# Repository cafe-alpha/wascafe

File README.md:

# wascafe

Wascafe ?
cafe-alpha's sandbox for wasca project, where I put sources for each PCB revision in a separate folder, and also where I learn how to use github related things.

Wasca ?
Sega Saturn multipurpose cartridge, still in development phase.
It will mimic Power Memory / Backup RAM, 1MB ROMs from KoF and Ultraman, and 1M/4M RAM expansion.
More than that, it should emulate Sega Saturn modems, and launch any 3rd party code, for example PseudoSaturn Kai.
Cart is based on Altera MAX 10 FPGA with external SDRAM and internal Nios II soft CPU. 

Wasca main repository can be found here : https://github.com/hitomi2500/wasca/

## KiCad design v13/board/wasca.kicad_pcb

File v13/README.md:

# Wasca version 1.3, by cafe-alpha, Autumn 2018

## Differences with v1.2
 - Communication with PC via FTDI
 - Expansion RAM emulation ... not working well
 - Stub of SPI communication with STM32 ... chip not available in this board

## About each directories
 - board : PCB sources
 - wasca_10m08scv4k_no_spi_20190420 : "stable" version of the firmware with only a minimal set of functions working.
 - wasca_10m08sc_20191205_abus_divide : attempt to make expansion RAM working ... which breaks several things.
 - WascaLoader : test bench for use on Saturn side, which contains several functionalities to test expansion RAM.

## How to compile firmware
 1. Quartus version used : 15.1.2 Lite
 2. Rebuild Qsys sources
 3. Compile the project
 4. In software -> wasca_test9 folder, load mk.bat
 5. Type "rb" and enter to rebuild NIOS part of the firmware

## Pictures :

More pictures and informations available on [my Saturn cartridges gallery](https://ppcenter.webou.net/satcart/gallery/#revw13).

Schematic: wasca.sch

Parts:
C1, C4: 4.7uF; C_0603_HandSoldering
C2, C3, C5, C6, C7, C8, C12, C13, C15, C40, C43, C45, C48, C49, C50, C51, C151, C152, C154: 0.1uF; SM0603
C16: 10uF; C_1206_HandSoldering
C29, C30, C31, C32, C33, C34, C35, C36, C37, C38, C39, C41, C42, C44, C46, C47: 0.1uF; C_0603_HandSoldering
C91, C153: 4.7uF; SM0603
CN1: CARTRIDGE_EDGE_CONNECTOR; CARTRIDGE_EDGE_CONNECTOR2
JTAG1: AVR-JTAG-10; JTAG_Header
LEDG1: LED; LED-3MM
LEDO1: LED; LED_0805
LEDR1: LED; LED-3MM
R12, R13, R14: 10K; R_0603_HandSoldering
R15: 1K; SM0603
R16, R17, R61, R62, R153: 10K; SM0603
R91, R92: 51K; SM0603
R152: 4K7; SM0603
R155, R156: 470; SM0603
R421, R422, R423: 470; R_0603_HandSoldering
RX_LED1: LED; LED_0805
SD1: SD_CARD; sd_socket
SW1: SWITCH_INV; NINJA_SW
TX_LED1: LED; LED_0805
U1, U2, U3, U4, U11: 74ALVC164245; TSSOP-48_6.1x12.5mm_Pitch0.5mm
U5: LD1117S33CTR; SOT-223
U8: 10M08SCE144I7G; TQFP144_ALTERA_HANDSOLDERING
U9: SDRAM_MT48_x16; TSOPII54_SDRAM_MT48
U151: FT232RL; SSOP28
X1, X61: CONN_02X02; Pin_Header_Straight_2x02
X2: CONN_01X02; Pin_Header_Straight_1x02_Pitch2.54mm
X4: CONN_01X04; Pin_Header_Straight_1x04
X151: USB-MB-S; con-usb-USB-MB-S

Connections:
/+3_3V: C5.1, C6.1, C12.1, C13.1, C16.1, C29.1, C30.1, C31.1, C32.1, C33.1, C34.1, C35.1, C36.1, C37.1, C38.1, C39.1, C40.1, C41.1, C42.1, C43.1, C44.1, C45.1, C46.1, C47.1, C48.1, C49.1, C51.1, C91.1, JTAG1.4, R12.1, R13.1, R14.1, R16.1, R17.1, R61.1, R62.1, R91.1, R92.1, RX_LED1.2 (A), SD1.4 (VDD), TX_LED1.2 (A), U1.31 (VCCA), U1.42 (VCCA), U2.31 (VCCA), U2.42 (VCCA), U3.24 (2DIR), U3.31 (VCCA), U3.42 (VCCA), U4.31 (VCCA), U4.42 (VCCA), U5.2 (VO), U8.1 (VCC_ONE), U8.2 (VCCA6), U8.5 (VCCA3), U8.9 (VCCO1A), U8.23 (VCCO1B), U8.31 (VCCO2), U8.34 (VCCA2), U8.35 (VCCA1), U8.36 (VCC_ONE), U8.37 (VCC_ONE), U8.40 (VCCO3), U8.49 (VCCO3), U8.51 (VCC_ONE), U8.67 (VCCO4), U8.71 (VCCA5), U8.72 (VCC_ONE), U8.73 (VCC_ONE), U8.82 (VCCO5), U8.94 (VCCO6), U8.103 (VCCO6), U8.107 (VCCA3), U8.108 (VCC_ONE), U8.109 (VCC_ONE), U8.115 (VCC_ONE), U8.117 (VCCO7), U8.128 (VCCO8), U8.139 (VCCO8), U8.143 (VCCA4), U8.144 (VCC_ONE), U9.1 (VDD), U9.3 (VDD), U9.9 (VDD), U9.14 (VDD), U9.27 (VDD), U9.43 (VDD), U9.49 (VDD), U11.1 (1DIR), U11.31 (VCCA), U11.42 (VCCA), U151.4 (VCCIO), X1.2
/+5V: C1.1, C2.1, C3.1, C4.1, C7.1, C8.1, C15.1, C50.1, C151.1, C152.1, C153.1, CN1.A1 (VCC), CN1.A2 (VCC), CN1.A27 (VCC), CN1.A67 (VCC), CN1.B1 (VCC), CN1.B2 (VCC), CN1.B27 (VCC), CN1.B67 (VCC), U1.7 (VCCB), U1.18 (VCCB), U2.7 (VCCB), U2.18 (VCCB), U3.7 (VCCB), U3.18 (VCCB), U4.7 (VCCB), U4.18 (VCCB), U5.3 (VI), U11.7 (VCCB), U11.18 (VCCB), U151.20 (VCC), X1.4
/ABUS_3V_A16: U2.41 (1A4), U8.120 (DIFFIO_RX_T16p)
/ABUS_3V_A17: U2.40 (1A5), U8.119 (DIFFIO_RX_T10n)
/ABUS_3V_A18: U2.43 (1A3), U8.121 (DEV_CLRn/DIFFIO_RX_T16n)
/ABUS_3V_A19: U8.118 (DIFFIO_RX_T10p), U11.29 (2A5)
/ABUS_3V_A20: U2.44 (1A2), U8.122 (DEV_OE)
/ABUS_3V_A21: U8.114 (IO), U11.30 (2A4)
/ABUS_3V_A22: U2.46 (1A1), U8.123 (VREFB8N0)
/ABUS_3V_A23: U8.113 (IO), U11.32 (2A3)
/ABUS_3V_A24: U2.47 (1A0), U8.124 (DIFFIO_RX_T19p)
/ABUS_3V_A25: U8.112 (VREFB7N0), U11.33 (2A2)
/ABUS_3V_CS0: U3.40 (1A5), U8.132 (DIFFIO_RX_T22p)
/ABUS_3V_CS1: U3.46 (1A1), U8.127 (DIFFIO_RX_T19n)
/ABUS_3V_CS2: U3.41 (1A4), U8.131 (DIFFIO_RX_T20n)
/ABUS_3V_IRQ: U3.35 (2A1), U8.135 (IO)
/ABUS_3V_MUX0: U1.36 (2A0), U1.37 (1A7), U8.141 (DIFFIO_RX_T26n)
/ABUS_3V_MUX1: U1.35 (2A1), U1.38 (1A6), U8.140 (DIFFIO_RX_T26p)
/ABUS_3V_MUX2: R12.2, U1.33 (2A2), U1.40 (1A5), U8.138 (CONF_DONE/DIFFIO_RX_T24n)
/ABUS_3V_MUX3: U1.32 (2A3), U1.41 (1A4), U8.6 (DIFFIO_RX_L1n)
/ABUS_3V_MUX4: U4.32 (2A3), U4.41 (1A4), U8.17 (VREFB1N0)
/ABUS_3V_MUX5: U4.33 (2A2), U4.40 (1A5), U8.15 (JTAGEN)
/ABUS_3V_MUX6: U4.35 (2A1), U4.38 (1A6), U8.14 (DIFFIO_RX_L7p)
/ABUS_3V_MUX7: U4.36 (2A0), U4.37 (1A7), U8.13 (DIFFIO_RX_L7n)
/ABUS_3V_MUX8: U1.30 (2A4), U1.43 (1A3), U8.7 (DIFFIO_RX_L1p)
/ABUS_3V_MUX9: U1.29 (2A5), U1.44 (1A2), U8.8 (DIFFIO_RX_L3n)
/ABUS_3V_MUX10: U1.27 (2A6), U1.46 (1A1), U8.10 (DIFFIO_RX_L3p)
/ABUS_3V_MUX11: U1.26 (2A7), U1.47 (1A0), U8.11 (DIFFIO_RX_L5n)
/ABUS_3V_MUX12: U4.26 (2A7), U4.47 (1A0), U8.26 (CLK0n/DIFFIO_RX_L18n)
/ABUS_3V_MUX13: U4.27 (2A6), U4.46 (1A1), U8.24 (DIFFIO_RX_L16n)
/ABUS_3V_MUX14: U4.29 (2A5), U4.44 (1A2), U8.22 (DIFFIO_RX_L14p)
/ABUS_3V_MUX15: U4.30 (2A4), U4.43 (1A3), U8.21 (DIFFIO_RX_L14n)
/ABUS_3V_MUX_DATA_DIR: U1.1 (1DIR), U4.24 (2DIR), U8.12 (DIFFIO_RX_L5p)
/ABUS_3V_MUX_EN1: U1.25 (2OE), U4.48 (1OE), U8.25 (DIFFIO_RX_L16p)
/ABUS_3V_MUX_EN2: U1.48 (1OE), U4.25 (2OE), U8.27 (CLK0p/DIFFIO_RX_L18p`)
/ABUS_3V_RD: U3.47 (1A0), U8.126 (CONFIG_SEL)
/ABUS_3V_WAIT: U3.36 (2A0), U8.134 (CRC_ERROR/DIFFIO_RX_T22n)
/ABUS_3V_WR0: U3.43 (1A3), U8.130 (DIFFIO_RX_T20p)
/ABUS_3V_WR1: R14.2, U3.44 (1A2), U8.129 (nCONFIG)
/ABUS_A0: CN1.B45 (AA0), U4.12 (1B7)
/ABUS_A1: CN1.A45 (AA1), U1.13 (2B0)
/ABUS_A2: CN1.B44 (AA2), U4.11 (1B6)
/ABUS_A3: CN1.B43 (AA3), U4.9 (1B5)
/ABUS_A4: CN1.B42 (AA4), U4.8 (1B4)
/ABUS_A5: CN1.B40 (AA5), U4.6 (1B3)
/ABUS_A6: CN1.B39 (AA6), U4.5 (1B2)
/ABUS_A7: CN1.B38 (AA7), U4.3 (1B1)
/ABUS_A8: CN1.A40 (AA8), U1.19 (2B4)
/ABUS_A9: CN1.A42 (AA9), U1.17 (2B3)
/ABUS_A10: CN1.A44 (AA10), U1.14 (2B1)
/ABUS_A11: CN1.A43 (AA11), U1.16 (2B2)
/ABUS_A12: CN1.A38 (AA12), U1.22 (2B6)
/ABUS_A13: CN1.A39 (AA13), U1.20 (2B5)
/ABUS_A14: CN1.B37 (AA14), U4.2 (1B0)
/ABUS_A15: CN1.A37 (AA15), U1.23 (2B7)
/ABUS_A16: CN1.B35 (AA16), U2.8 (1B4)
/ABUS_A17: CN1.A35 (AA17), U2.9 (1B5)
/ABUS_A18: CN1.B34 (AA18), U2.6 (1B3)
/ABUS_A19: CN1.A34 (AA19), U11.20 (2B5)
/ABUS_A20: CN1.B33 (AA20), U2.5 (1B2)
/ABUS_A21: CN1.A33 (AA21), U11.19 (2B4)
/ABUS_A22: CN1.B32 (AA22), U2.3 (1B1)
/ABUS_A23: CN1.A32 (AA23), U11.17 (2B3)
/ABUS_A24: CN1.B31 (AA24), U2.2 (1B0)
/ABUS_A25: CN1.A31 (AA25), U11.16 (2B2)
/ABUS_CS0: CN1.A47 (ACS0), U3.9 (1B5)
/ABUS_CS1: CN1.B48 (ACS1), U3.3 (1B1)
/ABUS_CS2: CN1.A48 (ACS2), U3.8 (1B4)
/ABUS_D0: CN1.A55 (AD0), U1.12 (1B7)
/ABUS_D1: CN1.A56 (AD1), U1.11 (1B6)
/ABUS_D2: CN1.A57 (AD2), U1.9 (1B5)
/ABUS_D3: CN1.A58 (AD3), U1.8 (1B4)
/ABUS_D4: CN1.B58 (AD4), U4.17 (2B3)
/ABUS_D5: CN1.B57 (AD5), U4.16 (2B2)
/ABUS_D6: CN1.B56 (AD6), U4.14 (2B1)
/ABUS_D7: CN1.B55 (AD7), U4.13 (2B0)
/ABUS_D8: CN1.A60 (AD8), U1.6 (1B3)
/ABUS_D9: CN1.A61 (AD9), U1.5 (1B2)
/ABUS_D10: CN1.A62 (AD10), U1.3 (1B1)
/ABUS_D11: CN1.A63 (AD11), U1.2 (1B0)
/ABUS_D12: CN1.B63 (AD12), U4.23 (2B7)
/ABUS_D13: CN1.B62 (AD13), U4.22 (2B6)
/ABUS_D14: CN1.B61 (AD14), U4.20 (2B5)
/ABUS_D15: CN1.B60 (AD15), U4.19 (2B4)
/ABUS_IRQ: CN1.B53 (AIRQ), U3.14 (2B1)
/ABUS_RD: CN1.B47 (ARD), U3.2 (1B0)
/ABUS_WAIT: CN1.B52 (AWAIT), U3.13 (2B0)
/ABUS_WR0: CN1.A49 (AWR0), U3.6 (1B3)
/ABUS_WR1: CN1.B49 (AWR1), U3.5 (1B2)
/DDR_SPARE1: LEDO1.2 (A), U8.99 (DIFFIO_RX_R27p)
/DDR_SPARE2: R62.2, U8.100 (DIFFIO_RX_R28p), X61.3
/DDR_SPARE3: R61.2, SW1.2, U8.101 (DIFFIO_RX_R27n), X61.1
/IBCK: CN1.A5 (IBCK), U11.5 (1B2)
/IBCK_3V: U8.106 (DIFFIO_RX_R33n), U11.44 (1A2)
/ILRCK: CN1.A6 (ILRCK), U11.12 (1B7)
/ILRCK_3V: U8.110 (DIFFIO_RX_T1p), U11.37 (1A7)
/ISD: CN1.A4 (ISD), U11.3 (1B1)
/ISD_3V: U8.105 (DIFFIO_RX_R33p), U11.46 (1A1)
/JTAG_TCK: JTAG1.1, R15.1, U8.18 (TCK/DIFFIO_RX_L11p)
/JTAG_TDI: JTAG1.9, R17.2, U8.19 (TDI/DIFFIO_RX_L12n)
/JTAG_TDO: JTAG1.3, U8.20 (TDO/DIFFIO_RX_L12p)
/JTAG_TMS: JTAG1.5, R16.2, U8.16 (TMS/DIFFIO_RX_L11n)
/LEDG1: LEDG1.2 (A), U8.97 (VREFB6N0)
/LEDR1: LEDR1.2 (A), U8.98 (DPCLK2/DIFFIO_RX_R26n)
/M10_SPARE1: U8.29 (CLK1p/DIFFIO_RX_L20p), X2.1
/M10_SPARE2: U8.30 (VREFB2N0), X2.2
/M10_UART_RX: U8.32 (PLL_L_CLKOUTn/DIFFIO_RX_L27n), U151.1 (TXD)
/M10_UART_TX: U8.33 (PLL_L_CLKOUTp/DIFFIO_RX_L27p), U151.5 (RXD)
/RESET: CN1.A3 (SYSRES), U11.13 (2B0)
/RESET_3V: U8.111 (DIFFIO_RX_T1n), U11.36 (2A0)
/SCSPCLK: CN1.A7 (SCSPCLK), U2.23 (2B7)
/SCSPCLK_3V: U2.26 (2A7), U8.28 (CLK1n/DIFFIO_RX_L20n)
/SDR_A0: U8.65 (DIFFIO_TX_RX_B23p), U9.23 (A0)
/SDR_A1: U8.66 (IO), U9.24 (A1)
/SDR_A2: U8.69 (DIFFIO_TX_RX_B27n), U9.25 (A2)
/SDR_A3: U8.70 (DIFFIO_TX_RX_B27p), U9.26 (A3)
/SDR_A4: U8.96 (DPCLK3/DIFFIO_RX_R26p), U9.29 (A4)
/SDR_A5: U8.93 (DIFFIO_RX_R18n), U9.30 (A5)
/SDR_A6: U8.92 (DIFFIO_RX_R18p), U9.31 (A6)
/SDR_A7: U8.91 (CLK3n/DIFFIO_RX_R16n), U9.32 (A7)
/SDR_A8: U8.90 (CLK3p/DIFFIO_RX_R16p), U9.33 (A8)
/SDR_A9: U8.89 (CLK2n/DIFFIO_RX_R14n), U9.34 (A9)
/SDR_A10: U8.64 (DIFFIO_TX_RX_B23n), U9.22 (A10)
/SDR_A11: U8.88 (CLK2p/DIFFIO_RX_R14p), U9.35 (A11)
/SDR_A12: U8.87 (DIFFIO_RX_R10n), U9.36 (A12)
/SDR_BA0: U8.61 (VREFB4N0), U9.20 (BA0)
/SDR_BA1: U8.62 (IO), U9.21 (BA1)
/SDR_CAS: U8.58 (DIFFIO_TX_RX_B14p), U9.17 (nCAS)
/SDR_CKE: U8.86 (DIFFIO_RX_R11n), U9.37 (CKE)
/SDR_CLK: U8.85 (DIFFIO_RX_R10p), U9.38 (CLK)
/SDR_CS: U8.60 (DIFFIO_TX_RX_B16p), U9.19 (nCS)
/SDR_DQ0: U8.45 (DIFFIO_TX_RX_B5p), U9.2 (DQ0)
/SDR_DQ1: U8.46 (DIFFIO_TX_RX_B7n), U9.4 (DQ1)
/SDR_DQ2: U8.47 (DIFFIO_TX_RX_B7p), U9.5 (DQ2)
/SDR_DQ3: U8.48 (VREFB3N0), U9.7 (DQ3)
/SDR_DQ4: U8.50 (DIFFIO_TX_RX_B9n), U9.8 (DQ4)
/SDR_DQ5: U8.52 (DIFFIO_TX_RX_B9p), U9.10 (DQ5)
/SDR_DQ6: U8.54 (IO), U9.11 (DQ6)
/SDR_DQ7: U8.55 (DIFFIO_TX_RX_B12n), U9.13 (DQ7)
/SDR_DQ8: U8.81 (DIFFIO_RX_R7n), U9.42 (DQ8)
/SDR_DQ9: U8.80 (VREFB5N0), U9.44 (DQ9)
/SDR_DQ10: U8.79 (DIFFIO_RX_R7p), U9.45 (DQ10)
/SDR_DQ11: U8.78 (IO), U9.47 (DQ11)
/SDR_DQ12: U8.77 (DIFFIO_RX_R1n), U9.48 (DQ12)
/SDR_DQ13: U8.76 (DIFFIO_RX_R2n), U9.50 (DQ13)
/SDR_DQ14: U8.75 (DIFFIO_RX_R1p), U9.51 (DQ14)
/SDR_DQ15: U8.74 (DIFFIO_RX_R2p), U9.53 (DQ15)
/SDR_DQMH: U8.84 (DIFFIO_RX_R11p), U9.39 (UDQM-DQMH)
/SDR_DQML: U8.56 (DIFFIO_TX_RX_B12p), U9.15 (LDQM-DQML)
/SDR_RAS: U8.59 (DIFFIO_TX_RX_B16n), U9.18 (nRAS)
/SDR_WE: U8.57 (DIFFIO_TX_RX_B14n), U9.16 (nWE)
/SD_CLK: SD1.5 (CLK), U8.41 (DIFFIO_TX_RX_B3n), X4.3
/SD_CS: SD1.1 (CD/DAT3), U8.38 (DIFFIO_TX_RX_B1n), X4.1
/SD_DIN: SD1.2 (CMD), U8.39 (DIFFIO_TX_RX_B1p), X4.2
/SD_DOUT: R91.2, SD1.7 (DAT0), U8.44 (DIFFIO_TX_RX_B5n), X4.4
/SSEL: CN1.B3 (SSEL), U11.2 (1B0)
/SSEL_3V: U8.102 (DIFFIO_RX_R28n), U11.47 (1A0)
/UART_RXING: R155.1, U151.23 (CBUS0)
/UART_TXING: R156.1, U151.22 (CBUS1)
/WAIT_ENABLE: R13.2, U3.25 (2OE), U8.136 (nSTATUS/DIFFIO_RX_T24p)
GND: C1.2, C2.2, C3.2, C4.2, C5.2, C6.2, C7.2, C8.2, C12.2, C13.2, C15.2, C16.2, C29.2, C30.2, C31.2, C32.2, C33.2, C34.2, C35.2, C36.2, C37.2, C38.2, C39.2, C40.2, C41.2, C42.2, C43.2, C44.2, C45.2, C46.2, C47.2, C48.2, C49.2, C50.2, C51.2, C91.2, C151.2, C152.2, C153.2, C154.2, CN1.A8 (GND), CN1.A13 (GND), CN1.A18 (GND), CN1.A23 (GND), CN1.A29 (GND), CN1.A36 (GND), CN1.A41 (GND), CN1.A46 (GND), CN1.A54 (GND), CN1.A59 (GND), CN1.A64 (GND), CN1.A65 (GND), CN1.B7 (GND), CN1.B8 (GND), CN1.B13 (GND), CN1.B18 (GND), CN1.B23 (GND), CN1.B29 (GND), CN1.B36 (GND), CN1.B41 (GND), CN1.B46 (GND), CN1.B54 (GND), CN1.B59 (GND), CN1.B64 (GND), CN1.B65 (GND), JTAG1.2, JTAG1.10, R15.2, R153.1, R421.2, R422.2, R423.2, SD1.3 (VSS), SD1.6 (VSS), SD1.12 (SHELL1), SD1.13 (SHELL2), SD1.14 (SHELL3), SD1.15 (SHELL4), SD1.16 (CD_GND), SD1.17 (WP_GND), SW1.3, U1.4 (GND), U1.10 (GND), U1.15 (GND), U1.21 (GND), U1.24 (2DIR), U1.28 (GND), U1.34 (GND), U1.39 (GND), U1.45 (GND), U2.1 (1DIR), U2.4 (GND), U2.10 (GND), U2.11 (1B6), U2.12 (1B7), U2.13 (2B0), U2.14 (2B1), U2.15 (GND), U2.16 (2B2), U2.17 (2B3), U2.19 (2B4), U2.20 (2B5), U2.21 (GND), U2.22 (2B6), U2.24 (2DIR), U2.25 (2OE), U2.28 (GND), U2.34 (GND), U2.39 (GND), U2.45 (GND), U2.48 (1OE), U3.1 (1DIR), U3.4 (GND), U3.10 (GND), U3.11 (1B6), U3.12 (1B7), U3.15 (GND), U3.21 (GND), U3.26 (2A7), U3.27 (2A6), U3.28 (GND), U3.29 (2A5), U3.30 (2A4), U3.32 (2A3), U3.33 (2A2), U3.34 (GND), U3.39 (GND), U3.45 (GND), U3.48 (1OE), U4.1 (1DIR), U4.4 (GND), U4.10 (GND), U4.15 (GND), U4.21 (GND), U4.28 (GND), U4.34 (GND), U4.39 (GND), U4.45 (GND), U5.1 (GND), U8.3 (GND), U8.4 (GND), U8.42 (GND), U8.53 (GND), U8.63 (GND), U8.68 (GND), U8.83 (GND), U8.95 (GND), U8.104 (GND), U8.116 (GND), U8.125 (GND), U8.133 (GND), U8.137 (GND), U8.142 (GND), U8.145 (EXP_PAD), U9.6 (GND), U9.12 (GND), U9.28 (GND), U9.41 (GND), U9.46 (GND), U9.52 (GND), U9.54 (GND), U11.4 (GND), U11.6 (1B3), U11.8 (1B4), U11.9 (1B5), U11.10 (GND), U11.11 (1B6), U11.14 (2B1), U11.15 (GND), U11.21 (GND), U11.22 (2B6), U11.23 (2B7), U11.24 (2DIR), U11.25 (2OE), U11.28 (GND), U11.34 (GND), U11.39 (GND), U11.45 (GND), U11.48 (1OE), U151.7 (GND), U151.18 (GND), U151.21 (GND), U151.25 (AGND), U151.26 (TEST), X1.1, X1.3, X61.2, X61.4, X151.GND
unnamed: C154.1, U151.17 (3V3OUT)
unnamed: LEDG1.1 (K), R422.1
unnamed: LEDO1.1 (K), R423.1
unnamed: LEDR1.1 (K), R421.1
unnamed: R92.2, SD1.10 (CARD_DETECT), U8.43 (DIFFIO_TX_RX_B3p)
unnamed: R152.1, R153.2, U151.19 (~RESET~)
unnamed: R152.2, X151.VBUS
unnamed: R155.2, RX_LED1.1 (K)
unnamed: R156.2, TX_LED1.1 (K)
unnamed: U151.15 (USBD+), X151.D+
unnamed: U151.16 (USBD-), X151.D-

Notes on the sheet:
Spare for DDR : - DDR_DQSH - DDR_DQSL - DDR_CLKN
Extra
External 5V power supply + 3V3 power output/check
SDRAM : shares 3V3 with MAX10 DDR : requires 2V5 power supply
--- Changelog --- V1.0 hitomi2500 : - Initial version with 10M04SFE, SDRAM, FT201XS V1.1 hitomi2500 : - Both DDR/SDRAM support - Added USB and bluetooth support - Sound I/O mapped to MAX10 V1.2 cafe-alpha : - Changed PCB shape and ICs position in order to fit Action Replay case - Changed MAX10 chip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
The power descriptor in the internal EEPROM of the FT232R should be programmed to a value of zero (self-powered).
Connection with PC
TODO: add footprint to help orientation for 3V3 buffers TODO: pin B45 isn't A0 and consequently all address pins must be shifted and re-routed. TODO: restrict address lines count to A0-A23 (no plan to use A24) TODO: Use PLL output pin (32 or 33) for SDRAM clock. Probably requires to change SDRAM ch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

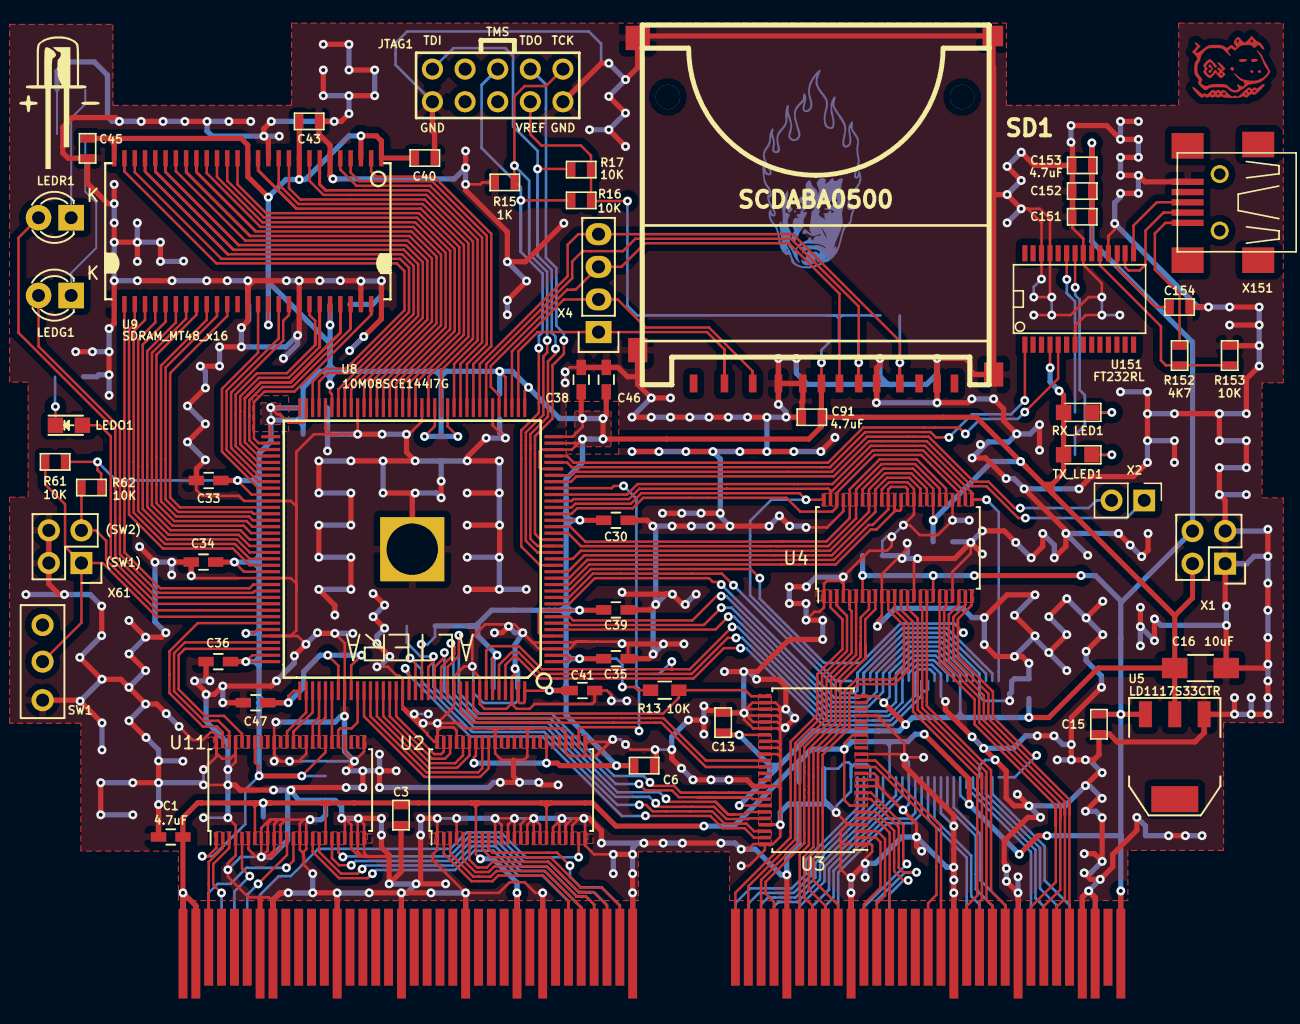
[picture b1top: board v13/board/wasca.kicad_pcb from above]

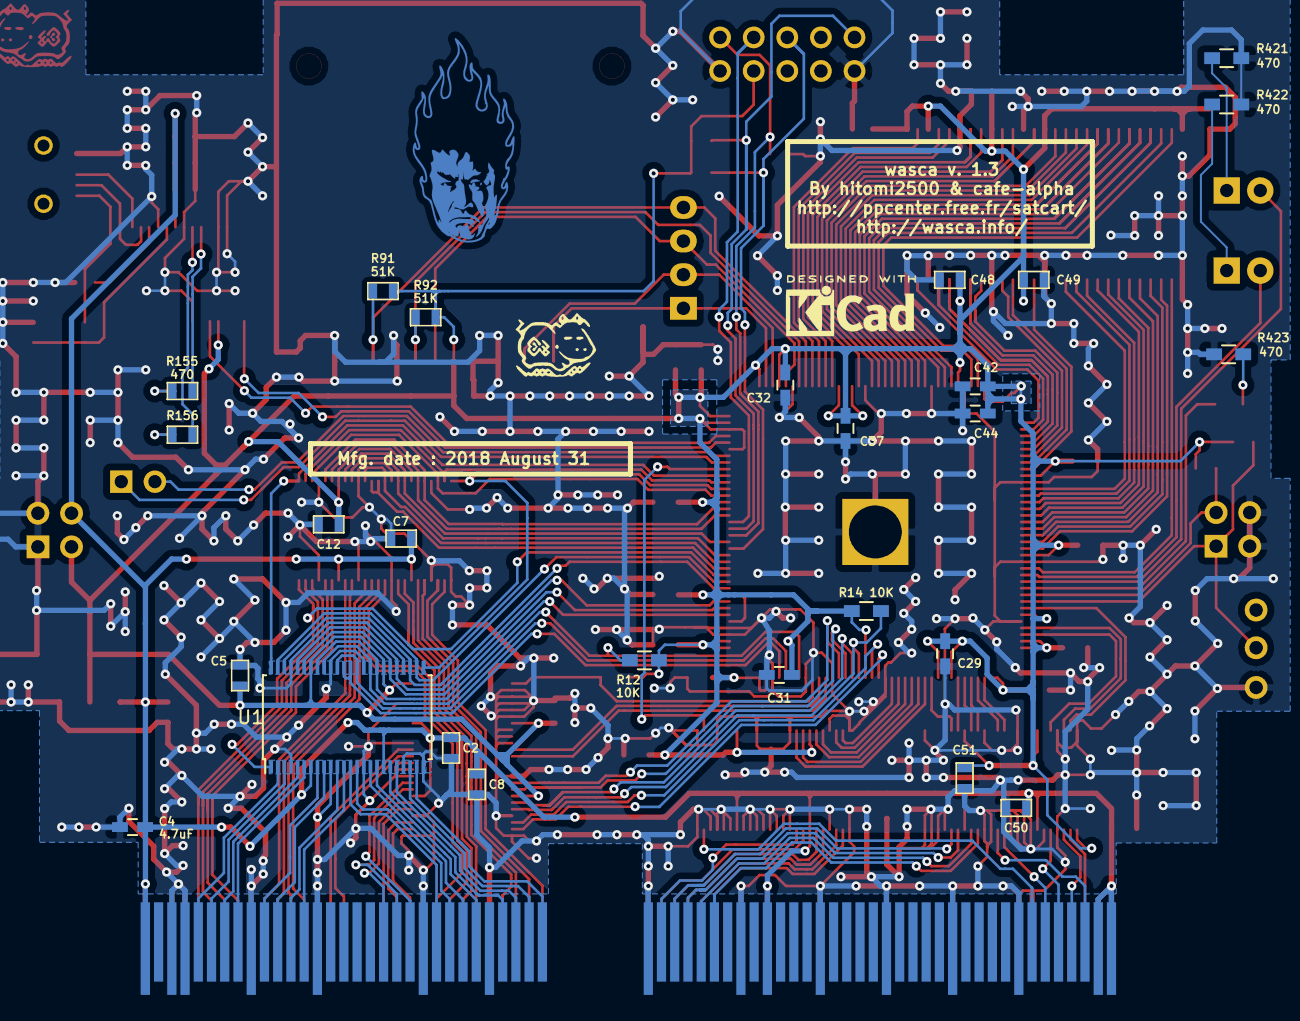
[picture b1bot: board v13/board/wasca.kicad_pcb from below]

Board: 2 copper layers, 80 parts (26 on the bottom side), 172 nets.

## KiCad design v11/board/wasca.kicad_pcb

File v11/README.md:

Second revision, by hitomi2500, Autumn 2015

Specs :
 - MAX10 FPGA (10M04SA or higher)
 - 32MB SDRAM/DDR support
 - USB and bluetooth interfaces
 - STM32 micro controller

Features :
 - Cartridge backup memory (volative)
 - SD (not SDHC) card access
 - RAM expansion (untested ?)

Pictures :

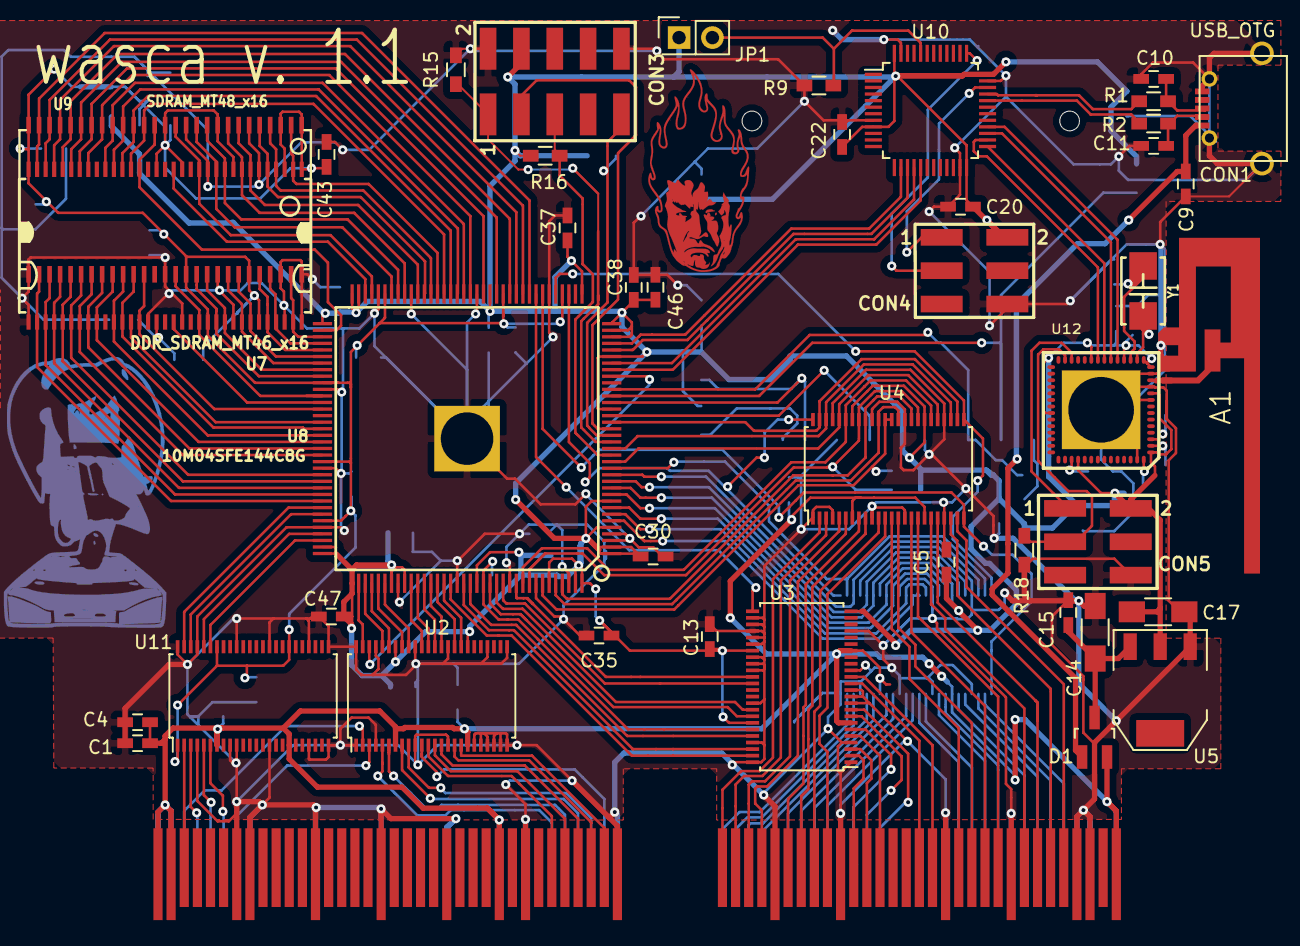
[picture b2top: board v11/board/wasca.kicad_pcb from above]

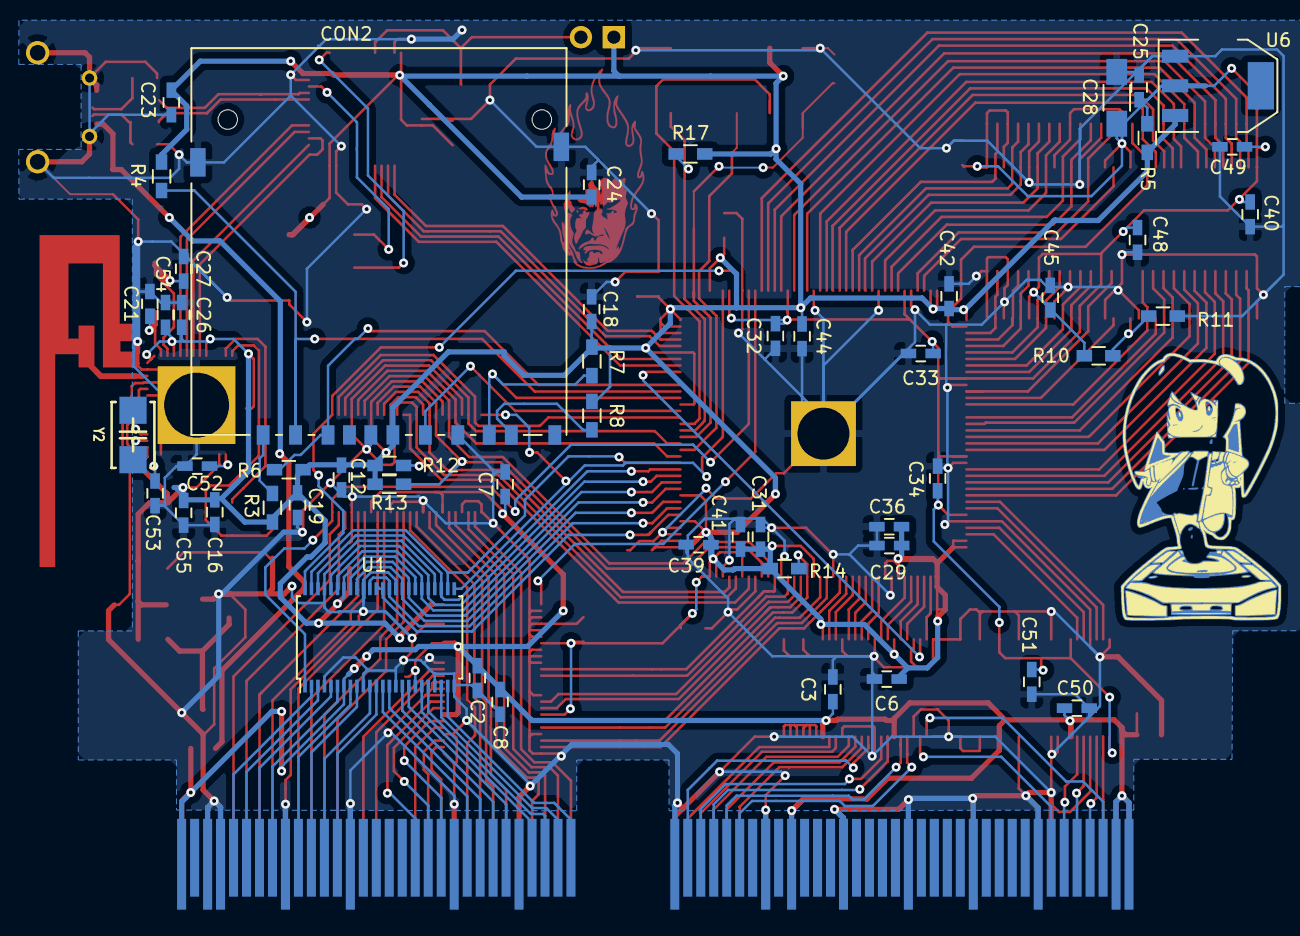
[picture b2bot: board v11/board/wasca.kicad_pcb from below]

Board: 2 copper layers, 96 parts (52 on the bottom side), 183 nets.

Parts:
A1: ANT; PCB_IF_ANT_2.4G
C1: 10uF; C_0603_HandSoldering
C2, C3, C4, C5, C6, C7, C8, C9, C12, C13, C15, C16, C19, C20, C21, C22, C23, C24, C25, C29, C30, C31, C32, C33, C34, C35, C36, C37, C38, C39, C40, C41, C42, C43, C44, C45, C46, C47, C48, C49, C50, C51, C54, C55: 0.1uF; C_0603_HandSoldering
C10, C11, C26, C27: 47pF; C_0603_HandSoldering
C14, C17, C28: 10uF; C_1206_HandSoldering
C18, C52, C53: 1uF; C_0603_HandSoldering
CN1: CARTRIDGE_EDGE_CONNECTOR; CARTRIDGE_EDGE_CONNECTOR2
CON1: USB_OTG; MicroUSB
CON2: SD_Card; SD_Card_Receptacle
CON3: AVR-JTAG-10; Pinhead_2x5_SMD
CON4, CON5: AVR-ISP-6; Pinhead_2x3_SMD
D1: D_Schottky_x2_KCom_AAK; SOT-23_Handsoldering
JP1: JUMPER; Pin_Header_Straight_2x01
R1, R2: 33; R_0603_HandSoldering
R3, R4, R6, R7, R8, R12, R13, R14: 50K; R_0603_HandSoldering
R5: DO NOT PLACE; R_0603_HandSoldering
R9, R15: 1K; R_0603_HandSoldering
R10, R11: 4.7K; R_0603_HandSoldering
R16, R17: 10K; R_0603_HandSoldering
R18: 12K; R_0603_HandSoldering
U1, U2, U3, U4, U11: 74ALVC164245; TSSOP-48_6.1x12.5mm_Pitch0.5mm
U5: LD1117S33CTR; SOT-223
U6: LD1117S25CTR; SOT-223
U7: DDR_SDRAM_MT46_x16; TSOP66_JEDEC_DDR_SDRAM
U8: 10M04SFE144C8G; TQFP144_ALTERA_HANDSOLDERING
U9: SDRAM_MT48_x16; TSOPII54_SDRAM_MT48
U10: STM32F042C6T6; LQFP-48_7x7mm_Pitch0.5mm
U12: CY8C4127LQI-BL473; QFN56_EXP
Y1: 24MHz; Crystal_5x3.2mm
Y2: 32678Hz; Crystal_5x3.2mm

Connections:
/+3_3V: C5.1, C6.1, C12.1, C13.1, C16.1, C17.1, C18.1, C19.1, C20.1, C21.1, C22.1, C23.1, C24.1, C29.1, C30.1, C31.1, C35.1, C36.1, C37.1, C38.1, C39.1, C41.1, C42.1, C44.1, C46.1, C47.1, C54.1, C55.1, CON2.4, CON3.4, CON4.2, CON5.2, JP1.1, R3.1, R4.1, R5.2, R6.1, R7.1, R8.1, R12.1, R13.1, R14.1, R16.1, R17.1, U1.31, U1.42, U2.31, U2.42, U3.24, U3.31, U3.42, U4.31, U4.42, U5.2, U6.3, U8.1, U8.2, U8.5, U8.9, U8.23, U8.31, U8.34, U8.35, U8.36, U8.37, U8.51, U8.71, U8.72, U8.73, U8.107, U8.108, U8.109, U8.115, U8.117, U8.128, U8.139, U8.143, U8.144, U10.9, U10.24, U10.36, U10.48, U12.1, U12.10, U12.14, U12.15, U12.18, U12.23, U12.36, U12.46
/+5V: C1.1, C2.1, C3.1, C4.1, C7.1, C8.1, C50.1, CN1.A1, CN1.A2, CN1.A27, CN1.A67, CN1.B1, CN1.B2, CN1.B27, CN1.B67, D1.2, U1.7, U1.18, U2.7, U2.18, U3.7, U3.18, U4.7, U4.18, U11.7, U11.18
/ABUS_3V_A16: U2.32, U8.123
/ABUS_3V_A17: U2.38, U8.118
/ABUS_3V_A18: U2.33, U8.122
/ABUS_3V_A19: U2.40, U8.114
/ABUS_3V_A20: U2.35, U8.121
/ABUS_3V_A21: U2.41, U8.113
/ABUS_3V_A22: U2.36, U8.120
/ABUS_3V_A23: U2.43, U8.112
/ABUS_3V_A24: U2.37, U8.119
/ABUS_3V_A25: U2.44, U8.111
/ABUS_3V_CS0: R14.2, U3.43, U8.129
/ABUS_3V_CS1: U3.46, U8.126
/ABUS_3V_CS2: U3.41, U8.130
/ABUS_3V_IRQ: U3.35, U8.134
/ABUS_3V_MUX0: U1.36, U1.37, U8.6
/ABUS_3V_MUX1: U1.35, U1.38, U8.7
/ABUS_3V_MUX2: U1.33, U1.40, U8.8
/ABUS_3V_MUX3: U1.32, U1.41, U8.10
/ABUS_3V_MUX4: R13.2, U4.32, U4.41, U8.136
/ABUS_3V_MUX5: U4.33, U4.40, U8.141
/ABUS_3V_MUX6: U4.35, U4.38, U8.140
/ABUS_3V_MUX7: R12.2, U4.36, U4.37, U8.138
/ABUS_3V_MUX8: U1.30, U1.43, U8.11
/ABUS_3V_MUX9: U1.29, U1.44, U8.12
/ABUS_3V_MUX10: U1.27, U1.46, U8.13
/ABUS_3V_MUX11: U1.26, U1.47, U8.14
/ABUS_3V_MUX12: U4.26, U4.47, U8.21
/ABUS_3V_MUX13: U4.27, U4.46, U8.17
/ABUS_3V_MUX14: U4.29, U4.44, U8.15
/ABUS_3V_MUX15: U4.30, U4.43, U8.135
/ABUS_3V_MUX_DATA_DIR: U1.1, U4.24, U8.43
/ABUS_3V_MUX_EN1: U1.25, U4.48, U8.39
/ABUS_3V_MUX_EN2: U1.48, U4.25, U8.41
/ABUS_3V_RD: U3.47, U8.124
/ABUS_3V_WAIT: U3.36, U8.132
/ABUS_3V_WR0: U3.40, U8.131
/ABUS_3V_WR1: U3.44, U8.127
/ABUS_A0: CN1.B45, U4.12
/ABUS_A1: CN1.A45, U1.13
/ABUS_A2: CN1.B44, U4.11
/ABUS_A3: CN1.B43, U4.9
/ABUS_A4: CN1.B42, U4.8
/ABUS_A5: CN1.B40, U4.6
/ABUS_A6: CN1.B39, U4.5
/ABUS_A7: CN1.B38, U4.3
/ABUS_A8: CN1.A40, U1.19
/ABUS_A9: CN1.A42, U1.17
/ABUS_A10: CN1.A44, U1.14
/ABUS_A11: CN1.A43, U1.16
/ABUS_A12: CN1.A38, U1.22
/ABUS_A13: CN1.A39, U1.20
/ABUS_A14: CN1.B37, U4.2
/ABUS_A15: CN1.A37, U1.23
/ABUS_A16: CN1.B35, U2.17
/ABUS_A17: CN1.A35, U2.11
/ABUS_A18: CN1.B34, U2.16
/ABUS_A19: CN1.A34, U2.9
/ABUS_A20: CN1.B33, U2.14
/ABUS_A21: CN1.A33, U2.8
/ABUS_A22: CN1.B32, U2.13
/ABUS_A23: CN1.A32, U2.6
/ABUS_A24: CN1.B31, U2.12
/ABUS_A25: CN1.A31, U2.5
/ABUS_CS0: CN1.A47, U3.6
/ABUS_CS1: CN1.B48, U3.3
/ABUS_CS2: CN1.A48, U3.8
/ABUS_D0: CN1.A55, U1.12
/ABUS_D1: CN1.A56, U1.11
/ABUS_D2: CN1.A57, U1.9
/ABUS_D3: CN1.A58, U1.8
/ABUS_D4: CN1.B58, U4.17
/ABUS_D5: CN1.B57, U4.16
/ABUS_D6: CN1.B56, U4.14
/ABUS_D7: CN1.B55, U4.13
/ABUS_D8: CN1.A60, U1.6
/ABUS_D9: CN1.A61, U1.5
/ABUS_D10: CN1.A62, U1.3
/ABUS_D11: CN1.A63, U1.2
/ABUS_D12: CN1.B63, U4.23
/ABUS_D13: CN1.B62, U4.22
/ABUS_D14: CN1.B61, U4.20
/ABUS_D15: CN1.B60, U4.19
/ABUS_IRQ: CN1.B53, U3.14
/ABUS_RD: CN1.B47, U3.2
/ABUS_WAIT: CN1.B52, U3.13
/ABUS_WR0: CN1.A49, U3.9
/ABUS_WR1: CN1.B49, U3.5
/BLUE_CLK: U10.26, U12.22
/BLUE_MISO: U10.27, U12.20
/BLUE_MOSI: U10.28, U12.19
/BLUE_SS: U10.25, U12.21
/COMM_CLK: U8.32, U10.15
/COMM_MISO: U8.30, U10.16
/COMM_MOSI: U8.29, U10.17
/COMM_SS: U8.33, U10.14
/DDR_CLKN: U7.46, U8.88
/DDR_DQSH: U7.51, U8.85
/DDR_DQSL: U7.16, U8.70
/IBCK: CN1.A5, U11.5
/IBCK_3V: U8.105, U11.44
/ILRCK: CN1.A6, U11.6
/ILRCK_3V: U8.106, U11.43
/ISD: CN1.A4, U11.3
/ISD_3V: U8.102, U11.46
/JTAG_TCK: CON3.1, R15.1, U8.18
/JTAG_TDI: CON3.9, R17.2, U8.19
/JTAG_TDO: CON3.3, U8.20
/JTAG_TMS: CON3.5, R16.2, U8.16
/RESET: CN1.A3, U2.2
/RESET_3V: U2.47, U8.110
/SCSPCLK: CN1.A7, U2.3
/SCSPCLK_3V: U2.46, U8.28
/SDR_A0: U7.29, U8.48, U9.23
/SDR_A1: U7.30, U8.47, U9.24
/SDR_A2: U7.31, U8.46, U9.25
/SDR_A3: U7.32, U8.45, U9.26
/SDR_A4: U7.35, U8.100, U9.29
/SDR_A5: U7.36, U8.99, U9.30
/SDR_A6: U7.37, U8.98, U9.31
/SDR_A7: U7.38, U8.97, U9.32
/SDR_A8: U7.39, U8.96, U9.33
/SDR_A9: U7.40, U8.93, U9.34
/SDR_A10: U7.28, U8.50, U9.22
/SDR_A11: U7.41, U8.92, U9.35
/SDR_A12: U7.42, U8.91, U9.36
/SDR_BA0: U7.26, U8.54, U9.20
/SDR_BA1: U7.27, U8.52, U9.21
/SDR_CAS: U7.22, U8.57, U9.17
/SDR_CKE: U7.44, U8.90, U9.37
/SDR_CLK: U7.45, U8.89, U9.38
/SDR_CS: U7.24, U8.55, U9.19
/SDR_DQ0: U7.2, U8.59, U9.2
/SDR_DQ1: U7.4, U8.60, U9.4
/SDR_DQ2: U7.5, U8.61, U9.5
/SDR_DQ3: U7.7, U8.62, U9.7
/SDR_DQ4: U7.8, U8.64, U9.8
/SDR_DQ5: U7.10, U8.65, U9.10
/SDR_DQ6: U7.11, U8.66, U9.11
/SDR_DQ7: U7.13, U8.69, U9.13
/SDR_DQ8: U7.54, U8.84, U9.42
/SDR_DQ9: U7.56, U8.81, U9.44
/SDR_DQ10: U7.57, U8.80, U9.45
/SDR_DQ11: U7.59, U8.79, U9.47
/SDR_DQ12: U7.60, U8.78, U9.48
/SDR_DQ13: U7.62, U8.77, U9.50
/SDR_DQ14: U7.63, U8.76, U9.51
/SDR_DQ15: U7.65, U8.75, U9.53
/SDR_DQMH: U7.47, U8.86, U9.39
/SDR_DQML: U7.20, U8.74, U9.15
/SDR_RAS: U7.23, U8.56, U9.18
/SDR_WE: U7.21, U8.58, U9.16
/SSEL: CN1.B3, U11.2
/SSEL_3V: U8.101, U11.47
/USB_VBUS: C9.1, CON1.1, D1.1
/VCC_SDRAM: C25.1, C28.1, C32.1, C33.1, C34.1, C40.1, C43.1, C45.1, C48.1, C49.1, C51.1, R5.1, R10.2, U6.2, U7.1, U7.3, U7.9, U7.15, U7.18, U7.33, U7.55, U7.61, U8.40, U8.49, U8.67, U8.82, U8.94, U8.103, U9.1, U9.3, U9.9, U9.14, U9.27, U9.43, U9.49, U11.1, U11.31, U11.42
/WAIT_ENABLE: U3.25, U8.44
GND: A1.2, C1.2, C2.2, C3.2, C4.2, C5.2, C6.2, C7.2, C8.2, C9.2, C10.2, C11.2, C12.2, C13.2, C14.2, C15.2, C16.2, C17.2, C18.2, C19.2, C20.2, C21.2, C22.2, C23.2, C24.2, C25.2, C26.2, C27.2, C28.2, C29.2, C30.2, C31.2, C32.2, C33.2, C34.2, C35.2, C36.2, C37.2, C38.2, C39.2, C40.2, C41.2, C42.2, C43.2, C44.2, C45.2, C46.2, C47.2, C48.2, C49.2, C50.2, C51.2, C52.2, C53.2, C54.2, C55.2, CN1.A8, CN1.A13, CN1.A18, CN1.A23, CN1.A29, CN1.A36, CN1.A41, CN1.A46, CN1.A54, CN1.A59, CN1.A64, CN1.A65, CN1.B7, CN1.B8, CN1.B13, CN1.B18, CN1.B23, CN1.B29, CN1.B36, CN1.B41, CN1.B46, CN1.B54, CN1.B59, CN1.B64, CN1.B65, CON1.5, CON1.6, CON2.3, CON2.6, CON2.12, CON2.13, CON3.2, CON3.10, CON4.6, CON5.6, R9.1, R11.1, R15.2, R18.1, U1.4, U1.10, U1.15, U1.21, U1.24, U1.28, U1.34, U1.39, U1.45, U2.1, U2.4, U2.10, U2.15, U2.19, U2.20, U2.21, U2.22, U2.23, U2.24, U2.25, U2.28, U2.34, U2.39, U2.45, U2.48, U3.1, U3.4, U3.10, U3.11, U3.12, U3.15, U3.21, U3.26, U3.27, U3.28, U3.29, U3.30, U3.32, U3.33, U3.34, U3.39, U3.45, U3.48, U4.1, U4.4, U4.10, U4.15, U4.21, U4.28, U4.34, U4.39, U4.45, U5.1, U6.1, U7.6, U7.12, U7.34, U7.48, U7.52, U7.58, U7.64, U7.66, U8.3, U8.4, U8.42, U8.53, U8.63, U8.68, U8.83, U8.95, U8.104, U8.116, U8.125, U8.133, U8.137, U8.142, U8.145, U9.6, U9.12, U9.28, U9.41, U9.46, U9.52, U9.54, U10.8, U10.23, U10.35, U10.47, U11.4, U11.9, U11.10, U11.15, U11.21, U11.24, U11.25, U11.28, U11.34, U11.39, U11.45, U11.48, U12.9, U12.11, U12.13, U12.55, U12.57
unnamed: A1.1, U12.12
unnamed: C10.1, CON1.3, R1.2
unnamed: C11.1, CON1.2, R2.2
unnamed: C14.1, C15.1, D1.3, U5.3
unnamed: C26.1, U12.16, Y1.1
unnamed: C27.1, U12.17, Y1.2
unnamed: C52.1, U12.45
unnamed: C53.1, U12.56
unnamed: CON2.1, R4.2, U8.25
unnamed: CON2.2, R6.2, U8.26
unnamed: CON2.5, U8.22
unnamed: CON2.7, R7.2, U8.24
unnamed: CON2.8, R8.2
unnamed: CON2.9, R3.2
unnamed: CON4.1, U10.34
unnamed: CON4.3, U10.37
unnamed: CON5.1, U12.26
unnamed: CON5.3, R18.2, U12.27
unnamed: JP1.2, R9.2, U10.44
unnamed: R1.1, U10.33
unnamed: R2.1, U10.32
unnamed: R10.1, R11.2, U7.49
unnamed: U12.2, Y2.1
unnamed: U12.3, Y2.2

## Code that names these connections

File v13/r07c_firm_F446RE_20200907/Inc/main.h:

/* USER CODE BEGIN Header */
/**
  ******************************************************************************
  * @file           : main.h
  * @brief          : Header for main.c file.
  *                   This file contains the common defines of the application.
  ******************************************************************************
  * @attention
  *
  * <h2><center>&copy; Copyright (c) 2020 STMicroelectronics.
  * All rights reserved.</center></h2>
  *
  * This software component is licensed by ST under BSD 3-Clause license,
  * the "License"; You may not use this file except in compliance with the
  * License. You may obtain a copy of the License at:
  *                        opensource.org/licenses/BSD-3-Clause
  *
  ******************************************************************************
  */
/* USER CODE END Header */

/* Define to prevent recursive inclusion -------------------------------------*/
#ifndef __MAIN_H
#define __MAIN_H

#ifdef __cplusplus
extern "C" {
#endif

/* Includes ------------------------------------------------------------------*/
#include "stm32f4xx_hal.h"

/* Private includes ----------------------------------------------------------*/
/* USER CODE BEGIN Includes */

/* USER CODE END Includes */

/* Exported types ------------------------------------------------------------*/
/* USER CODE BEGIN ET */

/* USER CODE END ET */

/* Exported constants --------------------------------------------------------*/
/* USER CODE BEGIN EC */

/* USER CODE END EC */

/* Exported macro ------------------------------------------------------------*/
/* USER CODE BEGIN EM */

/* USER CODE END EM */

/* Exported functions prototypes ---------------------------------------------*/
void Error_Handler(void);

/* USER CODE BEGIN EFP */

/* USER CODE END EFP */

/* Private defines -----------------------------------------------------------*/
#define B1_Pin GPIO_PIN_13
#define B1_GPIO_Port GPIOC
#define USART_TX_Pin GPIO_PIN_2
#define USART_TX_GPIO_Port GPIOA
#define USART_RX_Pin GPIO_PIN_3
#define USART_RX_GPIO_Port GPIOA
#define LD2_Pin GPIO_PIN_5
#define LD2_GPIO_Port GPIOA
#define SPI_SYNC_Pin GPIO_PIN_6
#define SPI_SYNC_GPIO_Port GPIOA
#define SD_DOUT_Pin GPIO_PIN_8
#define SD_DOUT_GPIO_Port GPIOC
#define TMS_Pin GPIO_PIN_13
#define TMS_GPIO_Port GPIOA
#define TCK_Pin GPIO_PIN_14
#define TCK_GPIO_Port GPIOA
#define SD_CS_Pin GPIO_PIN_11
#define SD_CS_GPIO_Port GPIOC
#define SD_CLK_Pin GPIO_PIN_12
#define SD_CLK_GPIO_Port GPIOC
#define SD_DIN_Pin GPIO_PIN_2
#define SD_DIN_GPIO_Port GPIOD
#define SWO_Pin GPIO_PIN_3
#define SWO_GPIO_Port GPIOB
#define SD_DETECT_Pin GPIO_PIN_7
#define SD_DETECT_GPIO_Port GPIOB
/* USER CODE BEGIN Private defines */

/* USER CODE END Private defines */

#ifdef __cplusplus
}
#endif

#endif /* __MAIN_H */

/************************ (C) COPYRIGHT STMicroelectronics *****END OF FILE****/

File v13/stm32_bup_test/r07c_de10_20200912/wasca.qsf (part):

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#set_location_assignment PIN_P11 -to MAX10_CLK1_50
#set_location_assignment PIN_N14 -to MAX10_CLK2_50

# # Pin 26 : SCSPCLK, from SIM
# # Pin 28 : SMD CLK from same board as this MAX 10 chip
# # "SW3" is used to configure unused clock signal pin as input.
# #set_location_assignment PIN_26 -to clk_clk
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

# abus_slave_0_abus_waitrequest     : ABUS_3V_WAIT
# abus_slave_0_abus_interrupt       : ABUS_3V_IRQ                                -> redirected to an unassigned pin on connector
# abus_slave_0_abus_disableout      : WAIT_ENABLE = for 3V3 buffer control (OUT) -> redirected to DE10's LEDR[5]
set_location_assignment PIN_AA7 -to abus_slave_0_abus_waitrequest
set_location_assignment PIN_AA17 -to abus_slave_0_abus_interrupt
set_location_assignment PIN_C13 -to wait_enable

#set_location_assignment PIN_AB3 -to reset_reset_n
set_location_assignment PIN_AB6 -to reset_reset_n
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
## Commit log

2016-07-09 Board v1.2 (preliminary version)
2016-07-11 PCB update, added firmware stub
    Added USB mezzanine board
    Fixed SCSPCLK wiring
    Minor changes in cartridge routing
    Added MAX10 firmware stub
2016-08-04 Added v1.0 and v1.1 boards
2016-08-04 Removed yabause stuff
2016-11-17 Added Board v1.0 description and pictures
2016-11-17 Update README.md
    Added pictures, updated specs
2016-11-18 Added v1.1 pictures Added v1.1 README.md
2016-11-18 Added FPGA firmware for board v1.0
2016-11-18 Added v1.2 board, pictures and README.md
2016-11-19 Added MAX10 evaluation board picture
2020-08-09 Add board v1.3
2020-08-09 Add firmware sources for board v1.3
2020-08-09 Add partial sources of test bench for use on Saturn side Some parts rely on Pseudo Saturn Kai (WIP) and consequently aren't disclosed.
2020-08-09 Add readme for v1.3
2020-08-09 Fix readme
2020-08-14 Don't update wasca_link.h when it is not found in SatLink folder (in that case, it's safe to use existing one) Don't update m10_ver_infos.h when date format is not as expected
2020-08-15 Disable test of minipseudo when running from cartridge Pack executable into cartridge boot ROM
2020-08-22 Added "Feedback Test", which writes to CS1 when memory test error happened
2020-08-22 Added WascaLoader screenshot
2020-08-22 Scroll error display during infinite test
2020-08-27 Make minipseudo support possible when booting from cartridge ROM
2020-08-28 Don't show "Pseudo Saturn Kai boot failed" message when run from WascaLoader
2020-09-07 Added sample firmware for NUCLEO-F446RE board (Requires CubeMx to generate HAL source code from wasca.ioc)
2020-09-09 Never make user waiting when booting a CD-ROM
2020-09-21 Backup memory support on SD card via STM32
2020-09-28 Gather several blocks in a single SD card write on STM32 side (WIP)
2020-10-11 Move minipseudo in a location not used by commercial games
2020-10-13 SPI support WIP. Everything else untested.
2020-10-14 SPI seems to work better now
2020-10-25 Dual SPI works. Boot ROM loading and save data access implemented but not tested yet.

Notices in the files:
v13/stm32_bup_test/r07c_de10_20200912/wasca.qsf:
Copyright (C) 1991-2014 Altera Corporation. All rights reserved.
v11/board/wasca.kicad_pcb:
Distributed under GNU GENERAL PUBLIC LICENSE Version 2
